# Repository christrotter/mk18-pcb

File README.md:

# PRODUCTION UPDATE - SUPERSEDED
This has been superseded by the rev2 of this board: [mk19](https://github.com/christrotter/mk19-pcb)

Many lessons learned.  Chief among them - it works!  We were able to prove out the shift register method.

## Things to fix
- dpad col usage; rethink how to make the dpad customizable e.g. rkjxt change-of-mind
- bad tft pinout; ordering wrong
- tft should be 0.5mm 8-pin ffc, not jst
- missing resistor arrays, 10k
- if there is a pin that could be reconfigured, ensure there is a breakout for that?
- move cyboard to edge of board
- cyboard breakout pcbs...seriously consider this; the cable lengths are super short
- main to a larger ffc cable
- per-key 0.3mm extenders pcbs...?
- change macropad vertical to edge-of-board flat FFC
- 90-deg jst, how will this help?
- and how would we make it fit?  where would things work out best to avoid the pcb capture?
- really need to make this happen
- bigger solder pads; or rather, jumpers! for the handedness, power bypass
- re-think the led bypass stuff...
- the whole bypass thing doesn’t work like i’d thought
- spare gpio breakouts should be 2.54 spaced
- what would it look like to have dual TFT?
- indicator breakout
- really needs to be DI/DO pairs per block of LEDs
- main slats
- small slats
- indicators
- then dedicated power breakouts for each
- 5v/3.3v/gnd for debug
- 5v/gnd x3 for leds
- there’s something i thought of that i didn’t write down and here we are…
- need to provide for power input
- GeorgeN suggests VSYS, not VBUS
- section 4.5 of pico datasheet
- do we want a dedicated USB power in?

# mk18-pcb
The antithesis of 'keep it simple, stupid' - all the features, all the time.

Do you need to use the Cyboard flex-pcb system?  Multiple Falcon pcbs?  SPI devices?  32 pins for rows/cols?  Perhaps enough RGB to illumine your entire home?  Audio?  ADC?  Reset switch? Power and debug breakouts?  And use an existing RP Pico to do it?

Probably not, which is why I had to design my own pcb.  So here it is...

# design goals
- Provide a re-usable platform for the arcboards that includes all of the normal functions
- Make it possible to use the Cyboard flex-pcb system
- Minimize pin usage by moving cols/rows over to shift registers
- Reduce the amount of fiddly soldering and wire stripping a normal hand-wire requires of you
- usb-c interconnects

## feature details

- Raspberry PI Pico (RP2040) footprint - just add pin headers and solder away - or, solder right to pads
- keys provided through the Cyboard flex-pcb: https://www.cyboard.digital/product-page/dactyl-flex-pcbs
 - or, JST-XH 2.54 headers
- macropad using Cyboard flex-pcb keys, custom breakout pcb: https://github.com/christrotter/macropad-pcb (0.5mm pitch 16-pin FFC cable)
 - vertical FFC connector
- dpad using custom breakout pcb: https://github.com/christrotter/5way-pcb
 - diodes are configured for ROW2COL
- usb-c split connector w. tzarc-grade voltage protection
 - buuut included a solder pad jumper to bypass if needed
- split-handedness pin
- SPI breakouts
  - PMW33xx
  - LCD (e.g. GC9A01)
  - shift registers (595 for rows, 589 for cols)
- pin breakouts
 - power, debug, ADC, audio, reset
 - remaining GPIO pins
 - test points (SPI pins, serial pins, WS2818 before/after level shifting)
- led breakouts w. bypasses
 - keys
 - 2x falcon pcbs
 - indicator strip
 - screen-mounted external indicators via usb-c
 - pin for whatever else you want to add to the chain

## pcb features
- two-layer pcb w. dual ground planes tied w. vias
- components configured as per datasheets
- bypass capacitors!
- care taken to avoid power running alongside signal for too long

# schematic overview
## mcu

## keys

## peripherals

## usb connections

## breakouts

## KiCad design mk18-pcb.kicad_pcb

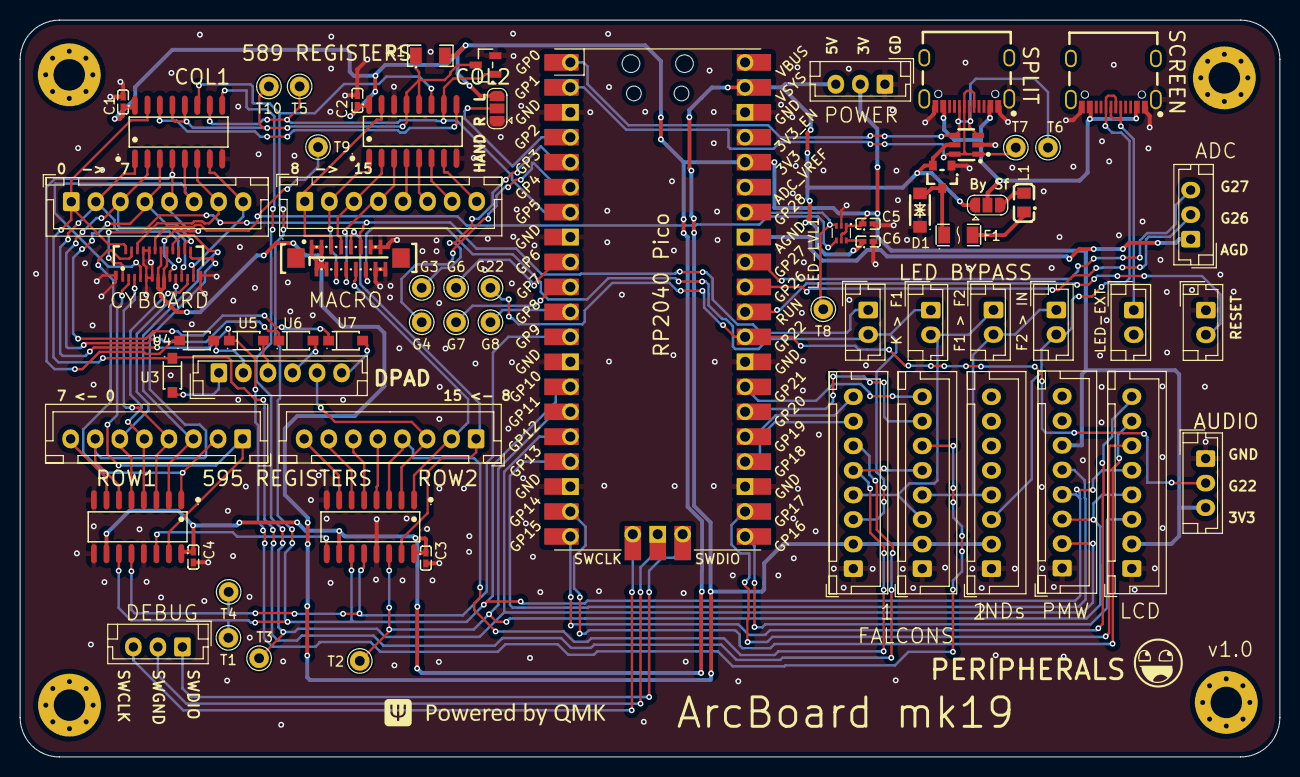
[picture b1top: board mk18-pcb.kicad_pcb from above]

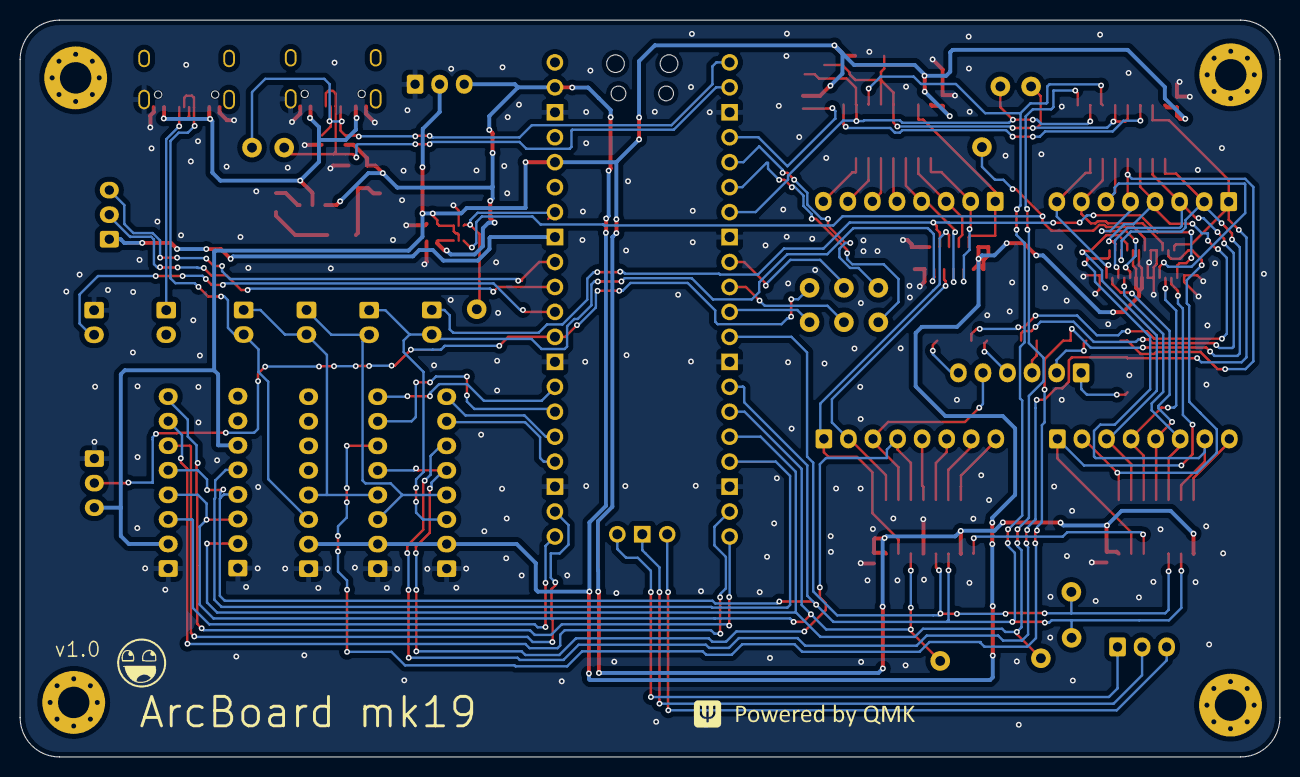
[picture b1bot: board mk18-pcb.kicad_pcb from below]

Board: 2 copper layers, 128.2 x 75.0 mm, 74 parts (2 on the bottom side), 85 nets.

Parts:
5WAY1: Conn_01x06_Socket; JST_EH_B6B-EH-A_1x06_P2.50mm_Vertical
ADC1: Conn_01x03_Socket; JST_EH_B3B-EH-A_1x03_P2.50mm_Vertical
AUDIO1: Conn_01x03_Socket; JST_EH_B3B-EH-A_1x03_P2.50mm_Vertical
C1, C2, C3, C4, C5, C6: 100nF; C0402
COL1, COL2: Conn_01x08_Socket; JST_XH_B8B-XH-A_1x08_P2.50mm_Vertical
COL_CS_MOS1: 2N7002; SOT-23-3_L2.9-W1.3-P1.90-LS2.4-BR
CYBOARD-MACRO1: HC-FPC-05-10-16RLTAG; FPC-SMD_16P-P0.50_HDGC_0.5K-A-16PBF
CYBOARD-MAIN1: ECT818001569; FPC-SMD_ECT818001569
D1: SMF5_0CA_C364279; SOD-123FL_L2.8-W1.8-LS3.7-BI
DBG1: Conn_01x03_Socket; JST_EH_B3B-EH-A_1x03_P2.50mm_Vertical
F1: MF-NSMF075-2; F1206
FAL1, FAL2: Conn_01x08_Socket; JST_XH_B8B-XH-A_1x08_P2.50mm_Vertical
G3, G4, G6, G7, G8, G22: Conn_01x01_Socket; Pin_D1.0mm_L10.0mm
H1, H2, H3, H4: MountingHole; MountingHole_3.2mm_M3_Pad_Via
HAND1: SolderJumper_3_Open; SolderJumper-3_P1.3mm_Open_RoundedPad1.0x1.5mm
IND1: Conn_01x08_Socket; JST_XH_B8B-XH-A_1x08_P2.50mm_Vertical
JP1: SolderJumper_3_Open; SolderJumper-3_P1.3mm_Open_RoundedPad1.0x1.5mm
L1: MPZ2012S101AT000; L0805
LCD1: Conn_01x08_Socket; JST_XH_B8B-XH-A_1x08_P2.50mm_Vertical
LED-EXT-DO1: Conn_01x02_Socket; JST_EH_B2B-EH-A_1x02_P2.50mm_Vertical
LED-FAL1, LED-FAL2: Conn_01x02_Socket; JST_EH_B2B-EH-A_1x02_P2.50mm_Vertical
LED-IND1: Conn_01x02_Socket; JST_EH_B2B-EH-A_1x02_P2.50mm_Vertical
LED-LVL1: SN74LVC1T45DRL; SOT-563_L1.6-W1.2-P0.50-LS1.6-BR
LED-MACRO1: Conn_01x02_Socket; JST_EH_B2B-EH-A_1x02_P2.50mm_Vertical
LOGO1, LOGO2: **REF; awesome-logo
LOGO3, LOGO4: **REF; qmk-lite
MOSFET1: AO3401A_C347476; SOT-23_L2.9-W1.3-P1.90-LS2.4-BR
PICO1: Pico; RPi_Pico_SMD_TH
PWM1: Conn_01x08_Socket; JST_XH_B8B-XH-A_1x08_P2.50mm_Vertical
PWR-OUT1: Conn_01x03_Socket; JST_EH_B3B-EH-A_1x03_P2.50mm_Vertical
R1: 1206W4F1002T5E; R1206
REG-COL1, REG-COL2: MC74HC589ADR2G; SOIC-16_L9.9-W3.9-P1.27-LS6.0-BL
REG-ROW1, REG-ROW2: 74HC595D; SOIC-16_L9.9-W3.9-P1.27-LS6.0-BL
RESET1: Conn_01x02_Socket; JST_EH_B2B-EH-A_1x02_P2.50mm_Vertical
ROW1, ROW2: Conn_01x08_Socket; JST_XH_B8B-XH-A_1x08_P2.50mm_Vertical
SCREEN1: TYPE-C-31-M-12; USB-C_SMD-TYPE-C-31-M-12
SPLIT-USB1: TYPE-C-31-M-12; USB-C_SMD-TYPE-C-31-M-12
T1, T2, T3, T4, T5, T6, T7, T8, T9, T10: Conn_01x01_Socket; Pin_D1.0mm_L10.0mm
U2: AZC199-04S-MS; TSOT-23-6_L2.9-W1.6-P0.95-LS2.8-BL
U3, U4, U5, U6, U7: 1N4148W_C81598; SOD-123F_L2.7-W1.6-LS3.8-RD

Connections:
+3V3: AUDIO1.3, C1.1, C2.1, C3.1, C4.1, C5.1, HAND1.3 (B), LCD1.2, LED-LVL1.1 (VCCA), LED-LVL1.5 (DIR), PICO1.36 (3V3), PWM1.6, PWR-OUT1.2, R1.2, REG-COL1.16 (VCC), REG-COL2.16 (VCC), REG-ROW1.10 (MasterReset), REG-ROW1.16 (VCC), REG-ROW2.10 (MasterReset), REG-ROW2.16 (VCC)
AGND: ADC1.1, PICO1.33 (AGND)
COL_CS: COL_CS_MOS1.1 (G), PICO1.7 (GPIO5), REG-COL1.10 (OE), REG-COL2.10 (OE), T5.1
COL_CS_MOS: COL_CS_MOS1.3 (D), R1.1, REG-COL1.12 (LATCH_CLOCK), REG-COL1.13 (SLOAD), REG-COL2.12 (LATCH_CLOCK), REG-COL2.13 (SLOAD), T10.1
GND: AUDIO1.1, C1.2, C2.2, C3.2, C4.2, C5.2, C6.2, COL_CS_MOS1.2 (S), CYBOARD-MACRO1.13, CYBOARD-MACRO1.14, CYBOARD-MACRO1.15, CYBOARD-MACRO1.16, CYBOARD-MAIN1.8, CYBOARD-MAIN1.9, CYBOARD-MAIN1.10, CYBOARD-MAIN1.11, CYBOARD-MAIN1.26, CYBOARD-MAIN1.27, D1.1 (K), FAL1.1, FAL2.1, HAND1.1 (A), IND1.1, LCD1.1, LED-LVL1.2 (GND), MOSFET1.1 (G), PICO1.3 (GND), PICO1.8 (GND), PICO1.13 (GND), PICO1.18 (GND), PICO1.23 (GND), PICO1.28 (GND), PICO1.38 (GND), PWM1.1, PWR-OUT1.1, REG-COL1.8 (GND), REG-COL1.14 (SA), REG-COL2.8 (GND), REG-ROW1.8 (GND), REG-ROW1.13 (OutputEnable), REG-ROW2.8 (GND), REG-ROW2.9 (Q7S), REG-ROW2.13 (OutputEnable), RESET1.1, SCREEN1.0 (SH), SCREEN1.A1 (GND), SCREEN1.A12 (GND), SCREEN1.B1 (GND), SCREEN1.B12 (GND), SPLIT-USB1.0 (SH), SPLIT-USB1.A1 (GND), SPLIT-USB1.A12 (GND), SPLIT-USB1.B1 (GND), SPLIT-USB1.B12 (GND), U2.2
GPIO3: G3.1, PICO1.5 (GPIO3)
GPIO4: G4.1, PICO1.6 (GPIO4)
GPIO6: G6.1, PICO1.9 (GPIO6)
GPIO7: G7.1, PICO1.10 (GPIO7)
GPIO8: G8.1, PICO1.11 (GPIO8)
GPIO22: AUDIO1.2, G22.1, PICO1.29 (GPIO22)
GPIO26: ADC1.2, PICO1.31 (GPIO26_ADC0)
GPIO27: ADC1.3, PICO1.32 (GPIO27_ADC1)
LCD_BL: LCD1.8, PICO1.20 (GPIO15)
LCD_CS: LCD1.3, PICO1.21 (GPIO16)
LCD_DC: LCD1.7, PICO1.19 (GPIO14)
LCD_RST: LCD1.6, PICO1.22 (GPIO17)
LED_DI_3.3V: LED-LVL1.3 (A), PICO1.34 (GPIO28_ADC2), T8.1
LED_FAL1_DI: CYBOARD-MACRO1.12, FAL1.3, LED-FAL1.1, LED-MACRO1.2
LED_FAL1_DO: FAL1.4, FAL2.3, LED-FAL1.2, LED-FAL2.1
LED_FAL2_DO: FAL2.4, IND1.4, LED-FAL2.2, LED-IND1.1
LED_INDICATORS_DO: IND1.3, LED-IND1.2, SCREEN1.A6 (DP1), SCREEN1.B6 (DP2)
LED_KEYS_DI: CYBOARD-MAIN1.12, LED-LVL1.4 (B), T9.1
LED_KEYS_DO: CYBOARD-MACRO1.11, CYBOARD-MAIN1.1, LED-MACRO1.1
LED_SCREEN_DO: LED-EXT-DO1.1, SCREEN1.A7 (DN1), SCREEN1.B7 (DN2)
unnamed: 5WAY1.1, U3.2 (A)
unnamed: 5WAY1.2, U4.2 (A)
unnamed: 5WAY1.3, U5.2 (A)
unnamed: 5WAY1.4, U6.2 (A)
unnamed: 5WAY1.6, U7.2 (A)
unnamed: D1.2 (A), F1.1, MOSFET1.3 (D)
unnamed: F1.2, L1.1
unnamed: HAND1.2 (C), PICO1.4 (GPIO2)
unnamed: JP1.3 (B), L1.2
unnamed: REG-COL1.9 (QH), REG-COL2.14 (SA)
unnamed: REG-ROW1.9 (Q7S), REG-ROW2.14 (DS)
PMW_CS: PICO1.17 (GPIO13), PWM1.5
ROW_CS: PICO1.12 (GPIO9), REG-ROW1.12 (StorageClock), REG-ROW2.12 (StorageClock), T4.1
SPI1_CLK: LCD1.5, PICO1.14 (GPIO10), PWM1.4, REG-COL1.11 (SHIFT_CLOCK), REG-COL2.11 (SHIFT_CLOCK), REG-ROW1.11 (ShiftClock), REG-ROW2.11 (ShiftClock), T1.1
SPI1_MISO: PICO1.16 (GPIO12), PWM1.2, REG-COL2.9 (QH), T3.1
SPI1_MOSI: LCD1.4, PICO1.15 (GPIO11), PWM1.3, REG-ROW1.14 (DS), T2.1
SWCLK: DBG1.3, PICO1.41 (SWCLK)
SWDIO: DBG1.1, PICO1.43 (SWDIO)
SWGND: DBG1.2, PICO1.42 (GND)
Serial_VBUS: JP1.2 (C), SCREEN1.A4 (VBUS), SCREEN1.A9 (VBUS), SCREEN1.B4 (VBUS), SCREEN1.B9 (VBUS), SPLIT-USB1.A4 (VBUS), SPLIT-USB1.A9 (VBUS), SPLIT-USB1.B4 (VBUS), SPLIT-USB1.B9 (VBUS)
Split_Comms_RX: PICO1.2 (GPIO1), SPLIT-USB1.A7 (DN1), SPLIT-USB1.B7 (DN2), T7.1, U2.1, U2.6
Split_Comms_TX: PICO1.1 (GPIO0), SPLIT-USB1.A6 (DP1), SPLIT-USB1.B6 (DP2), T6.1, U2.3, U2.4
VCC: C6.1, CYBOARD-MACRO1.1, CYBOARD-MACRO1.2, CYBOARD-MACRO1.3, CYBOARD-MACRO1.4, CYBOARD-MAIN1.13, CYBOARD-MAIN1.14, CYBOARD-MAIN1.15, CYBOARD-MAIN1.16, FAL1.2, FAL2.2, IND1.2, JP1.1 (A), LED-LVL1.6 (VCCB), MOSFET1.2 (S), PICO1.39 (VSYS), PWR-OUT1.3, U2.5
col0: COL1.1, CYBOARD-MAIN1.2, FAL1.6, REG-COL2.15 (A), U3.1 (K)
col1: COL1.2, CYBOARD-MAIN1.20, FAL2.6, REG-COL2.1 (B), U5.1 (K)
col2: COL1.3, CYBOARD-MAIN1.21, REG-COL2.2 (C), U6.1 (K)
col3: COL1.4, CYBOARD-MAIN1.22, REG-COL2.3 (D), U7.1 (K)
col4: COL1.5, CYBOARD-MAIN1.17, REG-COL2.4 (E), U4.1 (K)
col5: COL1.6, CYBOARD-MAIN1.7, REG-COL2.5 (F)
col6: COL1.7, CYBOARD-MAIN1.6, REG-COL2.6 (G)
col7: COL1.8, CYBOARD-MAIN1.25, REG-COL2.7 (H)
col8: COL2.1, CYBOARD-MACRO1.5, REG-COL1.15 (A)
col9: COL2.2, CYBOARD-MACRO1.6, REG-COL1.1 (B)
col10: COL2.3, CYBOARD-MACRO1.7, REG-COL1.2 (C)
col11: COL2.4, CYBOARD-MACRO1.8, REG-COL1.3 (D)
col12: COL2.5, REG-COL1.4 (E)
col13: COL2.6, REG-COL1.5 (F)
col14: COL2.7, REG-COL1.6 (G)
col15: COL2.8, REG-COL1.7 (H)
fal1-r1: FAL1.7, PICO1.24 (GPIO18)
fal1-r2: FAL1.8, PICO1.25 (GPIO19)
fal2-r1: FAL2.7, PICO1.26 (GPIO20)
fal2-r2: FAL2.8, PICO1.27 (GPIO21)
reset: PICO1.30 (RUN), RESET1.2
row0: CYBOARD-MAIN1.3, REG-ROW2.15 (Q0), ROW1.1
row1: CYBOARD-MAIN1.4, REG-ROW2.1 (Q1), ROW1.2
row2: CYBOARD-MAIN1.18, REG-ROW2.2 (Q2), ROW1.3
row3: CYBOARD-MAIN1.5, REG-ROW2.3 (Q3), ROW1.4
row4: CYBOARD-MAIN1.23, REG-ROW2.4 (Q4), ROW1.5
row5: CYBOARD-MAIN1.19, REG-ROW2.5 (Q5), ROW1.6
row6: CYBOARD-MAIN1.24, REG-ROW2.6 (Q6), ROW1.7
row7: REG-ROW2.7 (Q7), ROW1.8
row8: CYBOARD-MACRO1.9, REG-ROW1.15 (Q0), ROW2.1
row9: CYBOARD-MACRO1.10, REG-ROW1.1 (Q1), ROW2.2
row10: 5WAY1.5, REG-ROW1.2 (Q2), ROW2.3
row11: FAL1.5, FAL2.5, REG-ROW1.3 (Q3), ROW2.4
row12: REG-ROW1.4 (Q4), ROW2.5
row13: REG-ROW1.5 (Q5), ROW2.6
row14: REG-ROW1.6 (Q6), ROW2.7
row15: REG-ROW1.7 (Q7), ROW2.8

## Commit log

2023-11-19 initial commit of mk18-pcb files
2023-11-19 removing file bah
2023-12-29 adding some shift register info and other stuff
2023-12-29 flipping mosi on cols
2023-12-30 cleaning up save state
2023-12-30 removing autosave
2023-12-30 removing lock file
2023-12-31 capturing updates for the day
2024-01-01 work from the 31st
2024-01-03 jan2 updates, relocating shift registers
2024-01-03 adding design rules and jan3 updates. needs review now.
2024-01-04 getting ready to re-do the shift register routing so we can have pinouts.
2024-01-05 jan4 updates
2024-01-05 added bypass for safeties
2024-01-05 prior to removing pull-up resistors on comms
2024-01-06 jan6 updates, added 5way, moved all vias off silkscreen, added breakouts
2024-01-06 really close now maybe kinda
2024-01-06 added debug, test points, more
2024-01-06 preparing to redo some parts
2024-01-06 before updating the macropad connector
2024-01-06 replace two parts
2024-01-06 final commits, changing to some basic parts
2024-01-07 final production version of 1.0 woooo
2024-01-07 updating readme, tidied up schematic
2024-01-07 updating readme and doof
2024-01-07 updating doof pic
2024-02-13 final update, production notes and image
